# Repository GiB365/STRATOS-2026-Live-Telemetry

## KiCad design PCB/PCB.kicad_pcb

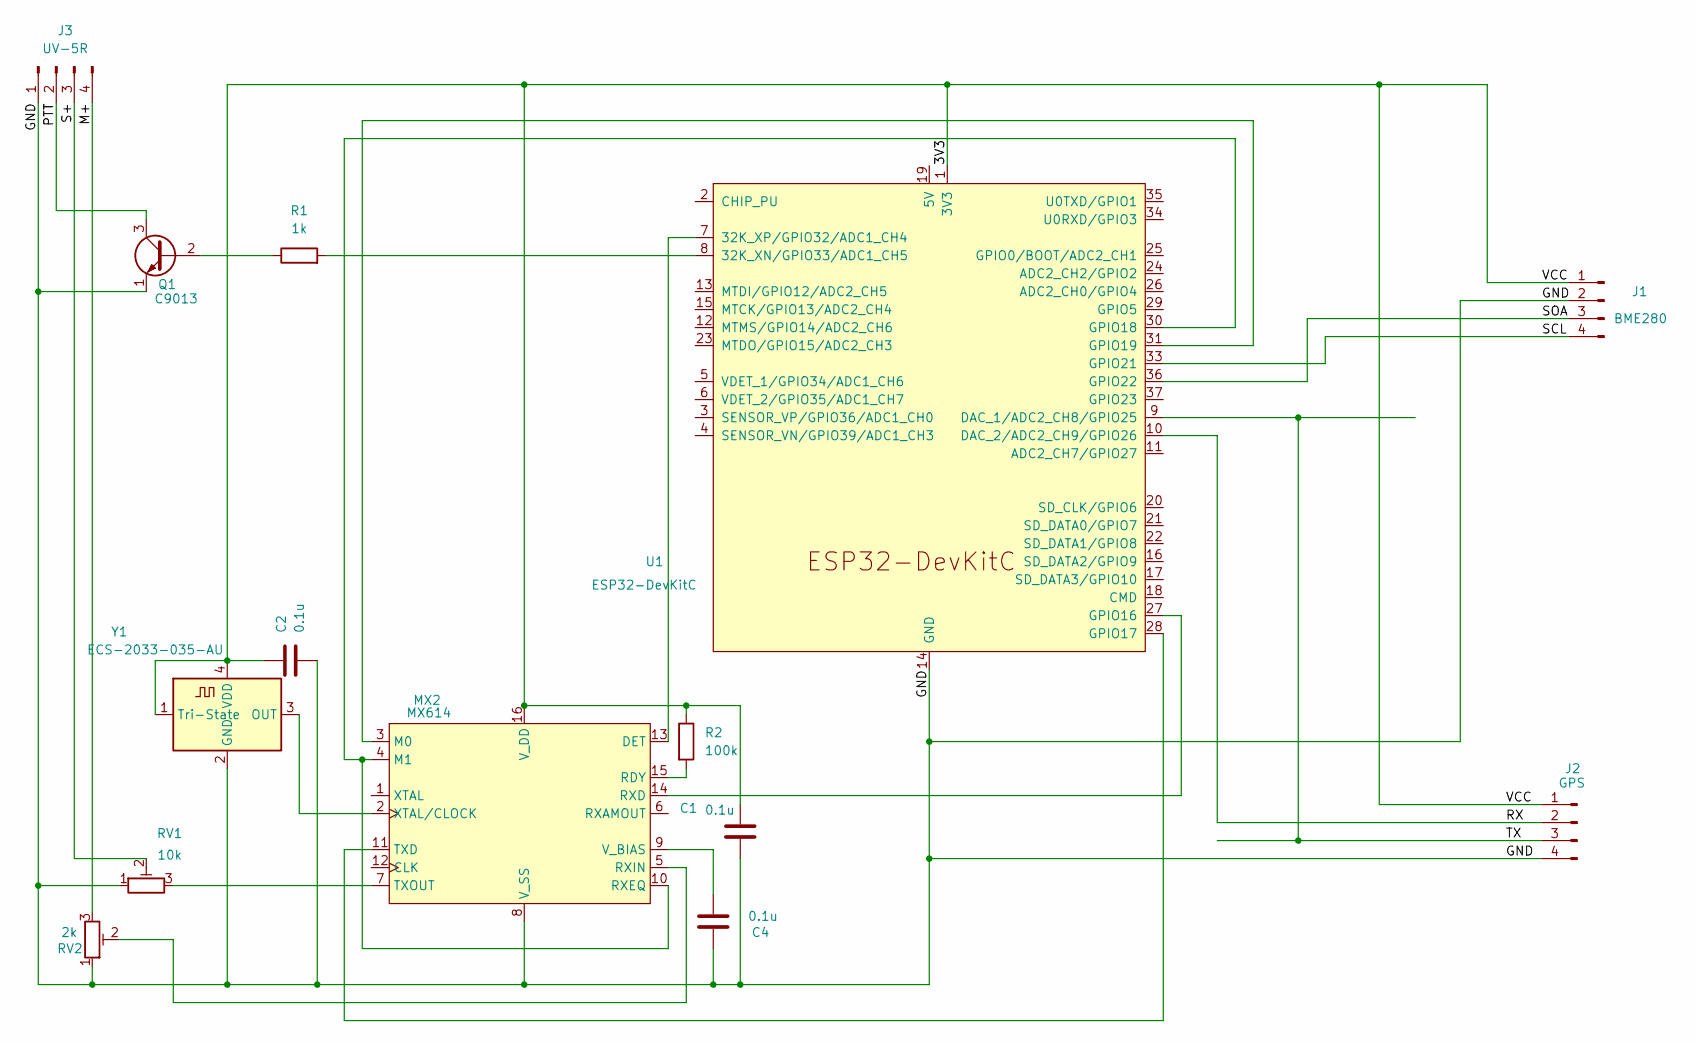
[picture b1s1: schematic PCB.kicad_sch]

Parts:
C1, C2, C4: 0.1u; C_0603_1608Metric_Pad1.08x0.95mm_HandSolder
J1: BME280; PinHeader_1x04_P2.54mm_Vertical
J2: GPS; PinHeader_1x04_P2.54mm_Vertical
J3: UV-5R; SolderWire-0.5sqmm_1x04_P4.8mm_D0.9mm_OD2.3mm
MX2: MX614; SOIC-16W_7.5x10.3mm_P1.27mm
Q1: C9013; TO-92_HandSolder
R1: 1k; R_Axial_DIN0207_L6.3mm_D2.5mm_P10.16mm_Horizontal
R2: 100k; R_Axial_DIN0207_L6.3mm_D2.5mm_P10.16mm_Horizontal
RV1: 10k; Potentiometer_Bourns_3386P_Vertical
RV2: 2k; Potentiometer_Bourns_3386P_Vertical
U1: ESP32-DevKitC
Y1: ECS-2033-035-AU; Oscillator_SMD_ECS_2520MV-xxx-xx-4Pin_2.5x2.0mm

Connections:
/3V3: C1.1, C2.1, J1.1, J2.1, MX2.16 (V_DD), R2.1, U1.1 (3V3), Y1.1 (Tri-State), Y1.4 (VDD)
/GND: C1.2, C2.2, C4.2, J1.2, J2.4, J3.1, MX2.8 (V_SS), Q1.1 (E), RV1.1, RV2.1, U1.14 (GND), U1.32 (GND), U1.38 (GND), Y1.2 (GND)
/M+: J3.4, RV2.3
/PTT: J3.2, Q1.3 (C)
/RX: J2.2, U1.10 (DAC_2/ADC2_CH9/GPIO26)
/S+: J3.3, RV1.2
/SCL: J1.4, U1.33 (GPIO21)
/SOA: J1.3, U1.36 (GPIO22)
/TX: J2.3, U1.9 (DAC_1/ADC2_CH8/GPIO25)
unnamed: MX2.13 (DET), U1.7 (32K_XP/GPIO32/ADC1_CH4)
unnamed: MX2.3 (M0), U1.31 (GPIO19)
unnamed: MX2.4 (M1), MX2.10 (RXEQ), U1.30 (GPIO18)
unnamed: MX2.15 (RDY), R2.2
unnamed: MX2.14 (RXD), U1.27 (GPIO16)
unnamed: MX2.5 (RXIN), RV2.2
unnamed: MX2.11 (TXD), U1.28 (GPIO17)
unnamed: MX2.7 (TXOUT), RV1.3
unnamed: C4.1, MX2.9 (V_BIAS)
unnamed: MX2.2 (XTAL/CLOCK), Y1.3 (OUT)
unnamed: Q1.2 (B), R1.1
unnamed: R1.2, U1.8 (32K_XN/GPIO33/ADC1_CH5)

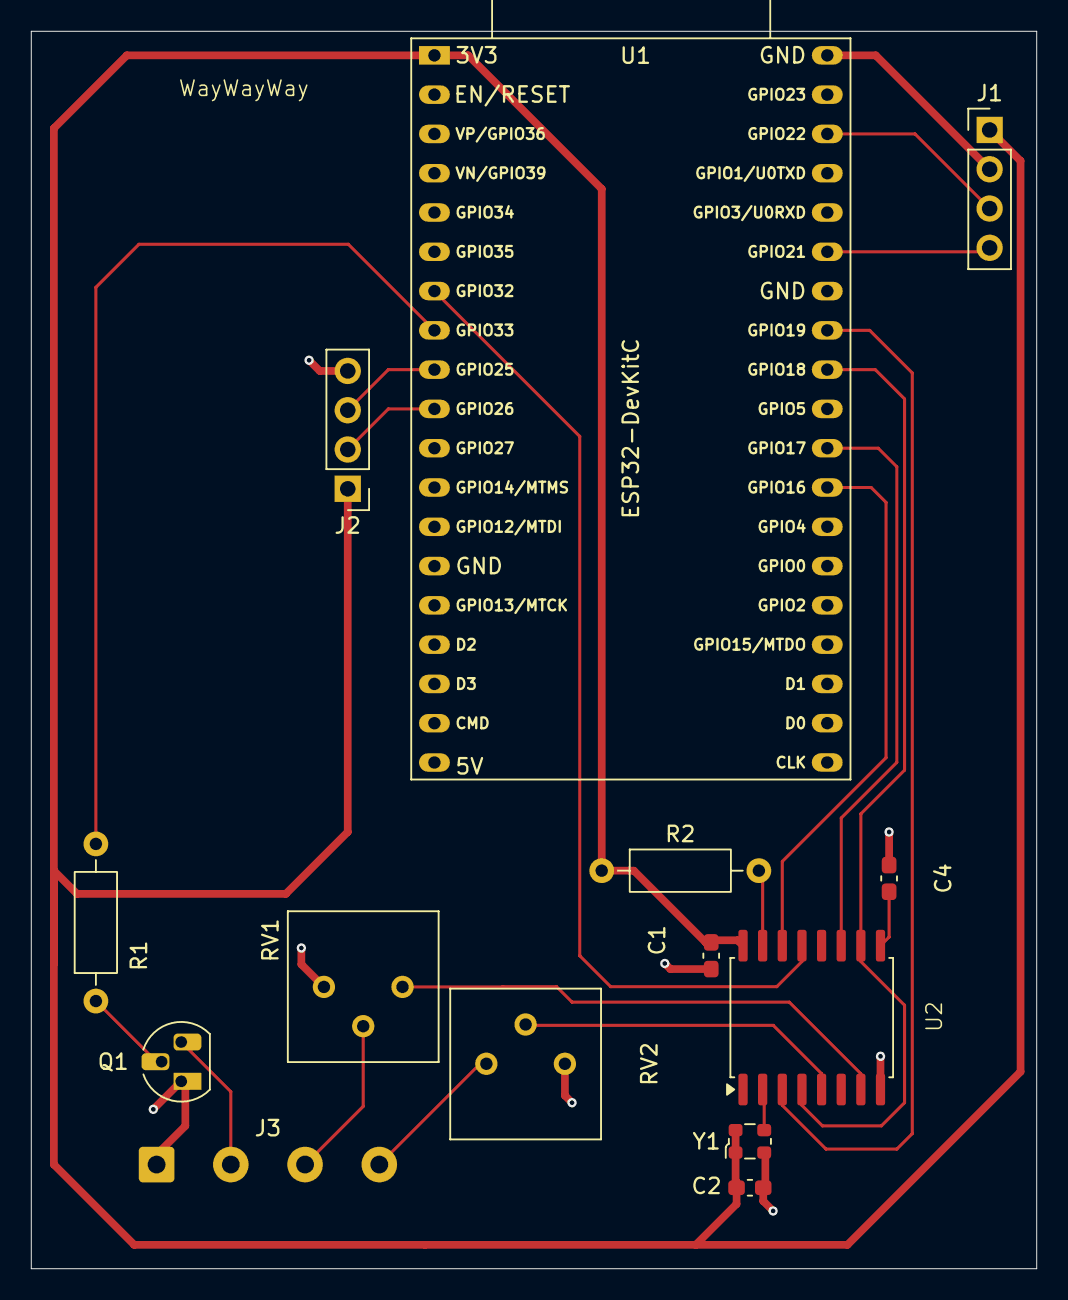
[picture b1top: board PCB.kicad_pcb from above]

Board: 2 copper layers, 65.0 x 80.0 mm, 14 parts (0 on the bottom side), 21 nets.
